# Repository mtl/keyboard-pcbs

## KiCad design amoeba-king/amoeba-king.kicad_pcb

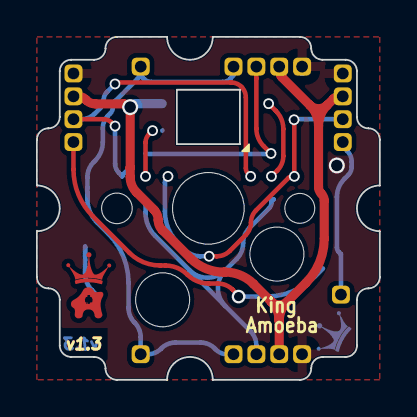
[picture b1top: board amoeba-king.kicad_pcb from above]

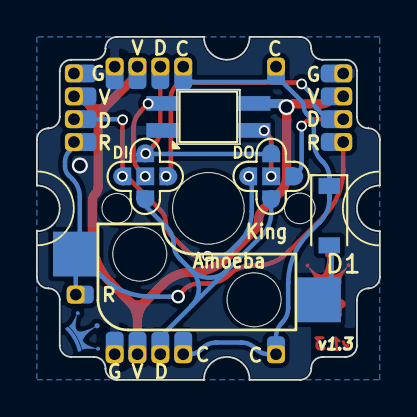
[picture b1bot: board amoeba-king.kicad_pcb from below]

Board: 2 copper layers, 19.0 x 19.1 mm, 15 parts (13 on the bottom side), 10 nets.

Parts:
Amoeba-Logo-Small: G***; amoeba-logo-small
D1: 1N4148W-7-F; D_SOD-123
J1, J4: Conn_01x04_Male; Header_1x04_P1.27mmL
J2, J3: Conn_01x04_Male; Header_1x04_P1.27mm
J5, J6, J7: Conn_01x01_Male; Header_1x01_P1.27mm
JP1, JP2: SolderJumper_5; SolderJumper-5_P1.3mm_Open_RoundedPad1.0x1.5mm
LED1: SK6812MINI_E; LED_SK6812MINI_E_PLCC4_3.2x2.8mm_Shine_Through
Royale: G***; royale
Royale#2: G***; royale
S1: MX1A; Kailh_MX_Socket

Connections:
/C: D1.1 (K), J2.1, J4.1, J5.1, J6.1
/DIN: JP1.2 (C), LED1.4 (DIN)
/GND: J1.4, J2.4, J3.4, J4.4, LED1.3 (VSS)
/R: J1.1, J3.1, J7.1, JP2.2 (C), S1.1
/VDD: J1.3, J2.3, J3.3, J4.3, LED1.1 (VDD)
unnamed: D1.2 (A), S1.2
unnamed: J1.2, JP1.1 (A), JP2.1 (A)
unnamed: J2.2, JP1.5 (E), JP2.5 (E)
unnamed: J3.2, JP1.3 (B), JP2.3 (B)
unnamed: J4.2, JP1.4 (D), JP2.4 (D)

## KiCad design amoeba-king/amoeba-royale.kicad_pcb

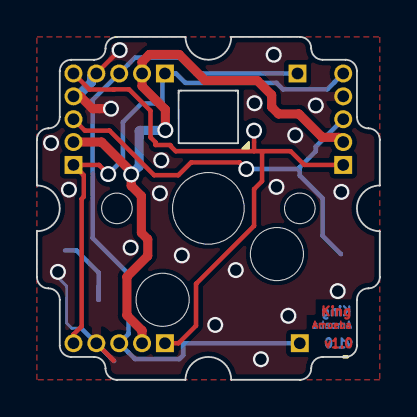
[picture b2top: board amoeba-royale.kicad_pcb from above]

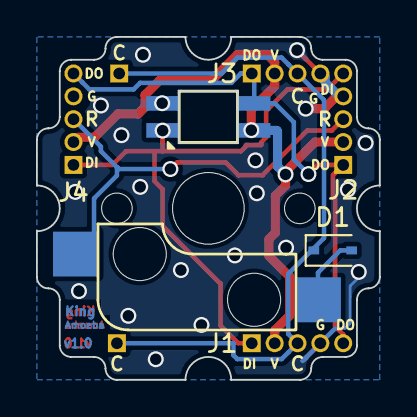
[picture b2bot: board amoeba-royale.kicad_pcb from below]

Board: 2 copper layers, 19.0 x 19.1 mm, 9 parts (9 on the bottom side), 7 nets.

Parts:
D1: 1N4148W-7-F; D_SOD-323
J1, J2, J4: Conn_01x05_Male; Header_1x05_P1.27mm
J3: Conn_01x04_Male; Header_1x04_P1.27mm
J5, J6: Conn_01x01_Male; Header_1x01_P1.27mm
LED1: SK6812MINI_E; LED_SK6812MINI_E_PLCC4_3.2x2.8mm_Shine_Through
S1: MX1A; Kailh_MX_Socket

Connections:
/C: D1.1, J1.3, J3.3, J5.1, J6.1
/DIN: J1.1, J2.5, J4.1, LED1.4
/DOUT: J1.5, J2.1, J3.1, J4.5, LED1.2
/GND: J1.4, J2.4, J3.4, J4.4, LED1.3
/R: J2.3, J4.3, S1.1
/VDD: J1.2, J2.2, J3.2, J4.2, LED1.1
unnamed: D1.2, S1.2

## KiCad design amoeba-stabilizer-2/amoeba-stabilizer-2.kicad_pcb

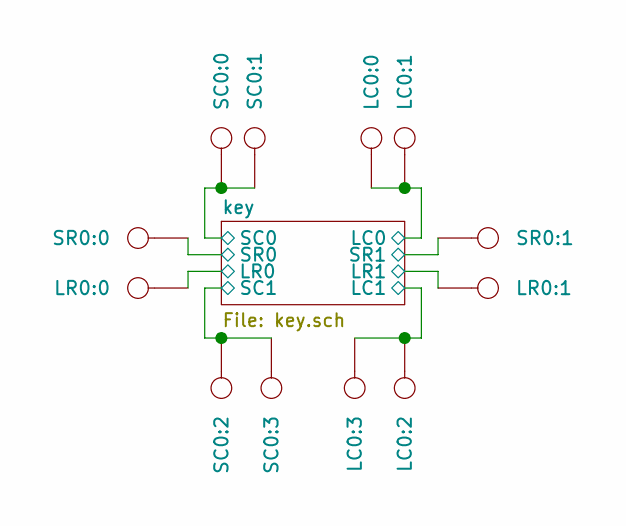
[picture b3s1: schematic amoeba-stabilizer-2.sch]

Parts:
LC0:0, LC0:1, LC0:2, LC0:3: CONN_1
LR0:0, LR0:1: CONN_1
SC0:0, SC0:1, SC0:2, SC0:3: CONN_1
SR0:0, SR0:1: CONN_1

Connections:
/key/LC0: LC0:0.1, LC0:1.1, LC0:2.1, LC0:3.1; also elsewhere on the board
/key/LR0: LR0:0.1, LR0:1.1; also elsewhere on the board
/key/SC0: SC0:0.1, SC0:1.1, SC0:2.1, SC0:3.1; also elsewhere on the board
/key/SR0: SR0:0.1, SR0:1.1; also elsewhere on the board

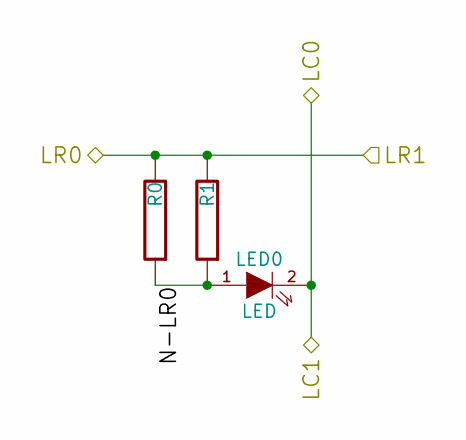
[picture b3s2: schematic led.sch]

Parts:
LED0: LED
R0, R1: RESISTOR

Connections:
/key/LC0: LED0.2 (K); also elsewhere on the board
/key/LR0: R0.2, R1.2; also elsewhere on the board
/key/led/N-LR0: LED0.1 (A), R0.1, R1.1

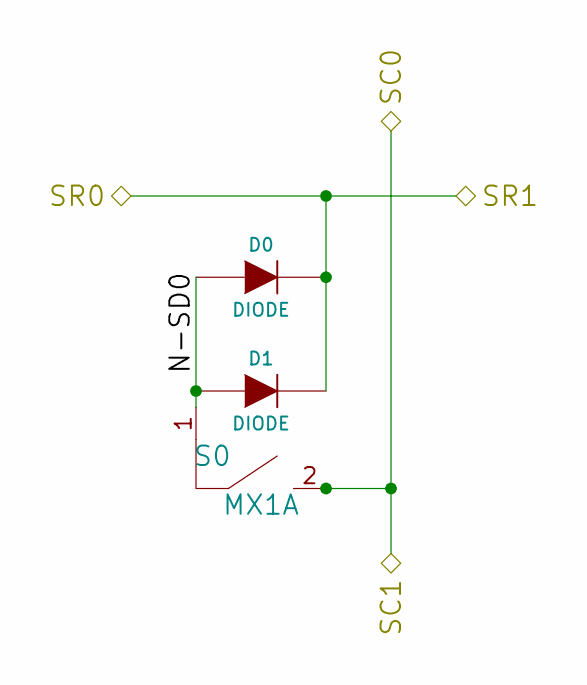
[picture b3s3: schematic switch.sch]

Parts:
D0, D1: DIODE
S0: MX1A

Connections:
/key/SC0: S0.2; also elsewhere on the board
/key/SR0: D0.2 (K), D1.2 (K); also elsewhere on the board
/key/switch/N-SD0: D0.1 (A), D1.1 (A), S0.1

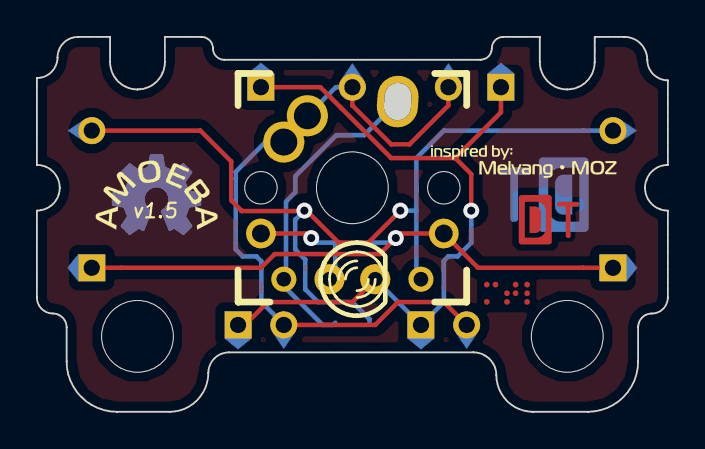
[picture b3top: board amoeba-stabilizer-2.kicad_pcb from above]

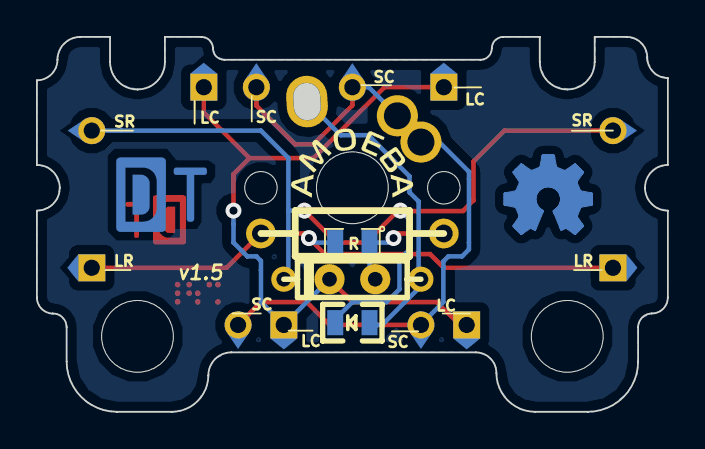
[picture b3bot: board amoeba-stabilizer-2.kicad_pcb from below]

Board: 2 copper layers, 35.1 x 20.8 mm, 38 parts (16 on the bottom side), 6 nets.

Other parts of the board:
amoeba-round: G***; amoeba-round
amoeba-round-rev: G***; amoeba-round-rev
dt-logo-big-rev: G***; dt-logo-big-rev
dt-logo-d: G***; dt-logo-d
dt-logo-t: G***; dt-logo-t
labels-melvang-moz: G***; labels-melvang-moz
mtl-braille: G***; mtl-braille
osh-logo-rev: G***; osh-logo-rev
pad-arrow-round: G***; pad-arrow-round
pad-arrow-round#2, pad-arrow-round#3, pad-arrow-round#4, pad-arrow-round#5, pad-arrow-round#6: G***; pad-arrow-round
pad-arrow-square: G***; pad-arrow-square
pad-arrow-square#2, pad-arrow-square#3, pad-arrow-square#4, pad-arrow-square#5, pad-arrow-square#6: G***; pad-arrow-square

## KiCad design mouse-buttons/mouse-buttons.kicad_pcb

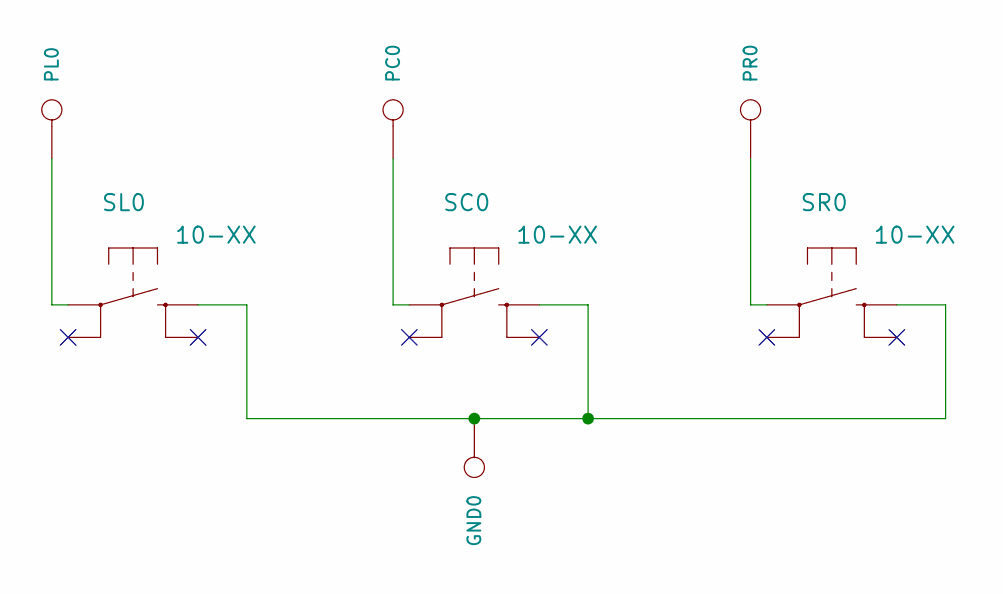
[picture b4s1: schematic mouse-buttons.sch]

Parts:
GND0: CONN_1
PC0: CONN_1
PL0: CONN_1
PR0: CONN_1
SC0: 10-XX; switch-omron-B3F-10XX
SL0: 10-XX; switch-omron-B3F-10XX
SR0: 10-XX; switch-omron-B3F-10XX

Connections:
unnamed: PL0.1, SL0.3
unnamed: PC0.1, SC0.3
unnamed: PR0.1, SR0.3
unnamed: GND0.1, SC0.1 (S), SL0.1 (S), SR0.1 (S)

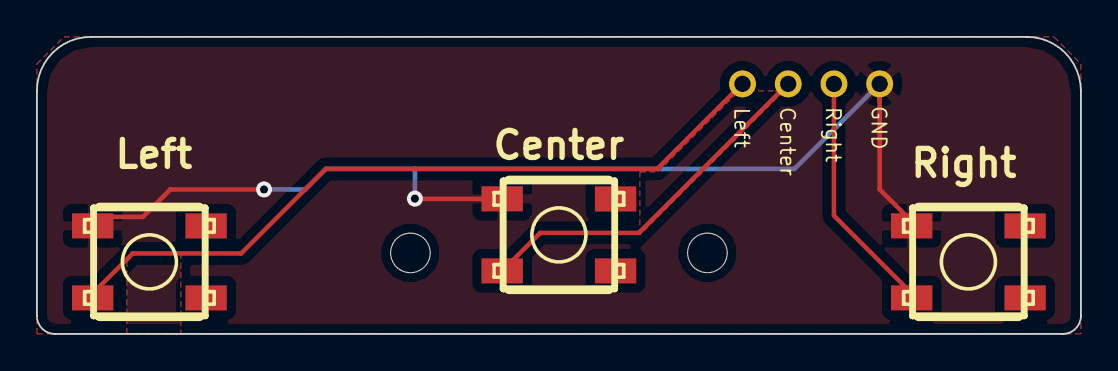
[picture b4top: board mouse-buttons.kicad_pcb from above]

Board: 2 copper layers, 58.0 x 16.5 mm, 7 parts (0 on the bottom side), 4 nets.

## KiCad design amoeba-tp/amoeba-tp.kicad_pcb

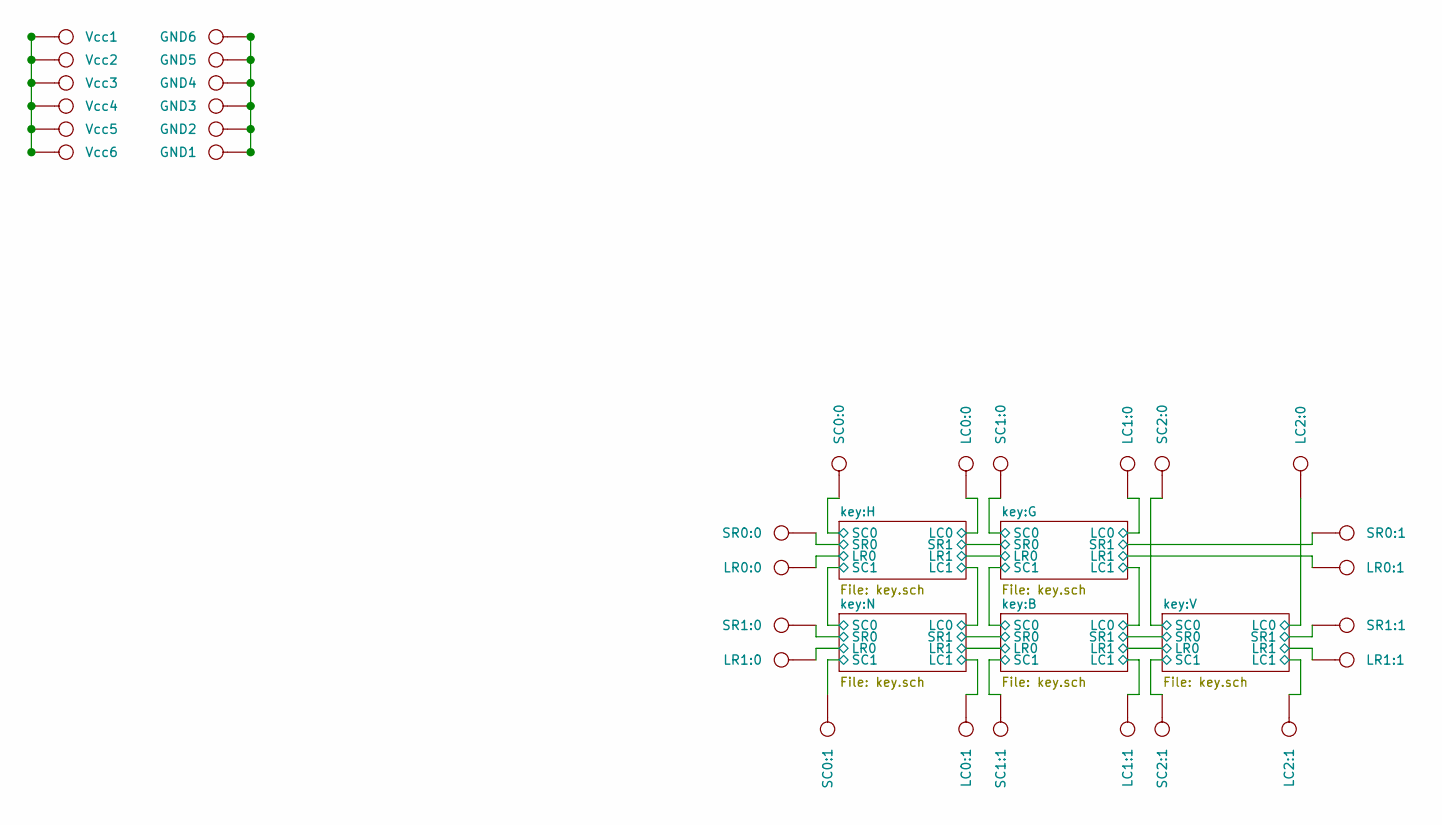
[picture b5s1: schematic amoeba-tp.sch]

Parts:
GND1, GND2, GND3, GND4, GND5, GND6: CONN_1
LC0:0, LC0:1, LC1:0, LC1:1, LC2:0, LC2:1: CONN_1
LR0:0, LR0:1, LR1:0, LR1:1: CONN_1
SC0:0, SC0:1, SC1:0, SC1:1, SC2:0, SC2:1: CONN_1
SR0:0, SR0:1, SR1:0, SR1:1: CONN_1
Vcc1, Vcc2, Vcc3, Vcc4, Vcc5, Vcc6: CONN_1

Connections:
/key:B/LC0: LC1:0.1, LC1:1.1; also elsewhere on the board
/key:B/LR0: LR1:0.1, LR1:1.1; also elsewhere on the board
/key:B/SC0: SC1:0.1, SC1:1.1; also elsewhere on the board
/key:B/SR0: SR1:0.1, SR1:1.1; also elsewhere on the board
/key:G/LR0: LR0:0.1, LR0:1.1; also elsewhere on the board
/key:G/SR0: SR0:0.1, SR0:1.1; also elsewhere on the board
/key:H/LC0: LC0:0.1, LC0:1.1; also elsewhere on the board
/key:H/SC0: SC0:0.1, SC0:1.1; also elsewhere on the board
/key:V/LC0: LC2:0.1, LC2:1.1; also elsewhere on the board
/key:V/SC0: SC2:0.1, SC2:1.1; also elsewhere on the board
unnamed: Vcc1.1, Vcc2.1, Vcc3.1, Vcc4.1, Vcc5.1, Vcc6.1
unnamed: GND1.1, GND2.1, GND3.1, GND4.1, GND5.1, GND6.1

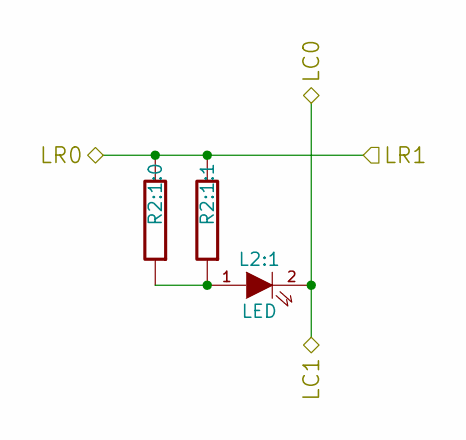
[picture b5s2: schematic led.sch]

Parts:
L0:0: LED
R0:0:0, R0:0:1: RESISTOR

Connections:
/key:G/LR0: R0:0:0.2, R0:0:1.2; also elsewhere on the board
/key:H/LC0: L0:0.2 (K); also elsewhere on the board
unnamed: L0:0.1 (A), R0:0:0.1, R0:0:1.1

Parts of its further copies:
L0:1, L1:0, L1:1, L2:1: LED
R0:1:0, R0:1:1, R1:0:0, R1:0:1, R1:1:0, R1:1:1, R2:1:0, R2:1:1: RESISTOR

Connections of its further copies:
/key:B/LC0: L1:0.2 (K), L1:1.2 (K); also elsewhere on the board
/key:B/LR0: R0:1:0.2, R0:1:1.2, R1:1:0.2, R1:1:1.2, R2:1:0.2, R2:1:1.2; also elsewhere on the board
/key:G/LR0: R1:0:0.2, R1:0:1.2; also elsewhere on the board
/key:H/LC0: L0:1.2 (K); also elsewhere on the board
/key:V/LC0: L2:1.2 (K); also elsewhere on the board
unnamed: L1:0.1 (A), R1:0:0.1, R1:0:1.1
unnamed: L0:1.1 (A), R0:1:0.1, R0:1:1.1
unnamed: L1:1.1 (A), R1:1:0.1, R1:1:1.1
unnamed: L2:1.1 (A), R2:1:0.1, R2:1:1.1

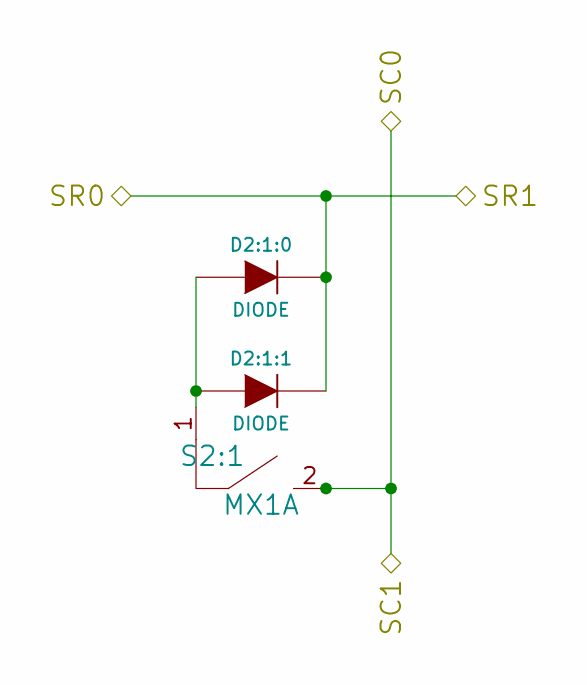
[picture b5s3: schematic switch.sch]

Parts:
D0:0:0, D0:0:1: DIODE
S0:0: MX1A

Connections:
/key:G/SR0: D0:0:0.2 (K), D0:0:1.2 (K); also elsewhere on the board
/key:H/SC0: S0:0.2; also elsewhere on the board
unnamed: D0:0:0.1 (A), D0:0:1.1 (A), S0:0.1

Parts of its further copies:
D0:1:0, D0:1:1, D1:0:0, D1:0:1, D1:1:0, D1:1:1, D2:1:0, D2:1:1: DIODE
S0:1, S1:0, S1:1, S2:1: MX1A

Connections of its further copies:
/key:B/SC0: S1:0.2, S1:1.2; also elsewhere on the board
/key:B/SR0: D0:1:0.2 (K), D0:1:1.2 (K), D1:1:0.2 (K), D1:1:1.2 (K), D2:1:0.2 (K), D2:1:1.2 (K); also elsewhere on the board
/key:G/SR0: D1:0:0.2 (K), D1:0:1.2 (K); also elsewhere on the board
/key:H/SC0: S0:1.2; also elsewhere on the board
/key:V/SC0: S2:1.2; also elsewhere on the board
unnamed: D1:0:0.1 (A), D1:0:1.1 (A), S1:0.1
unnamed: D0:1:0.1 (A), D0:1:1.1 (A), S0:1.1
unnamed: D1:1:0.1 (A), D1:1:1.1 (A), S1:1.1
unnamed: D2:1:0.1 (A), D2:1:1.1 (A), S2:1.1

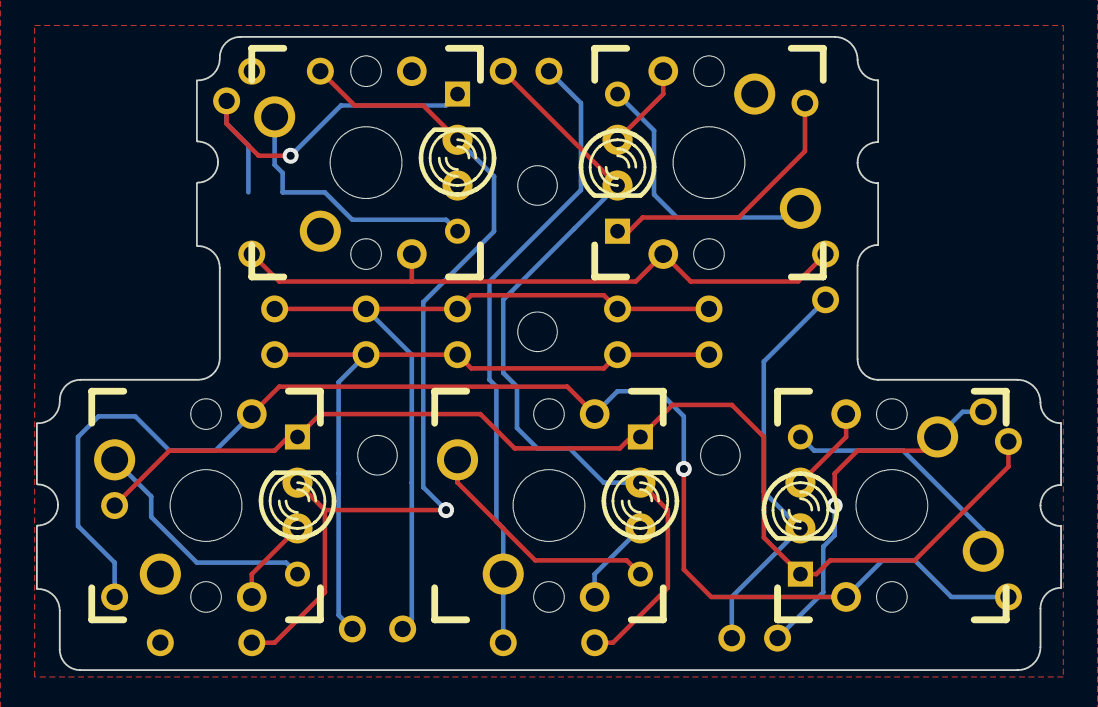
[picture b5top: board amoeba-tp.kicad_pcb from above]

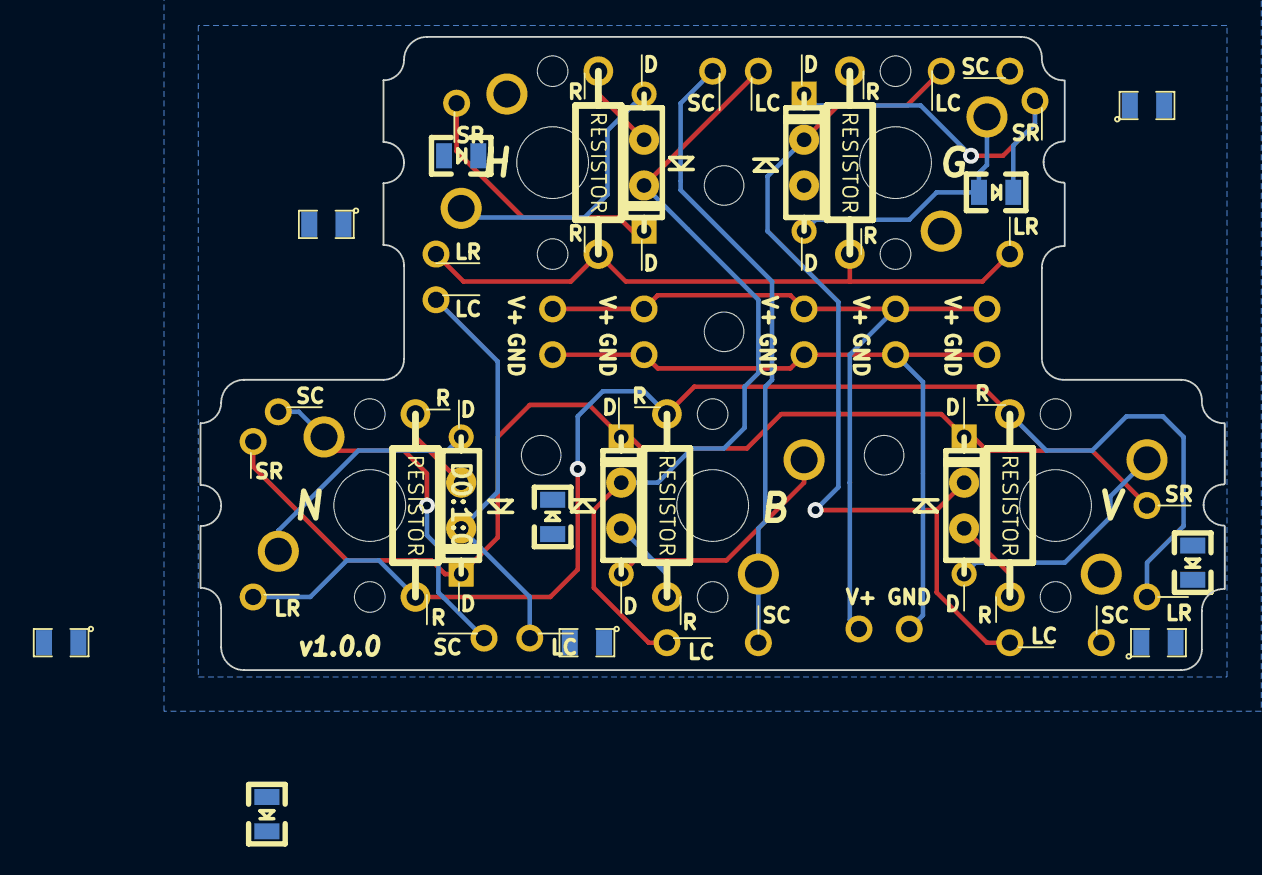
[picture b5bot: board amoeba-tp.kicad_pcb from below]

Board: 2 copper layers, 56.9 x 35.2 mm, 62 parts (20 on the bottom side), 22 nets.

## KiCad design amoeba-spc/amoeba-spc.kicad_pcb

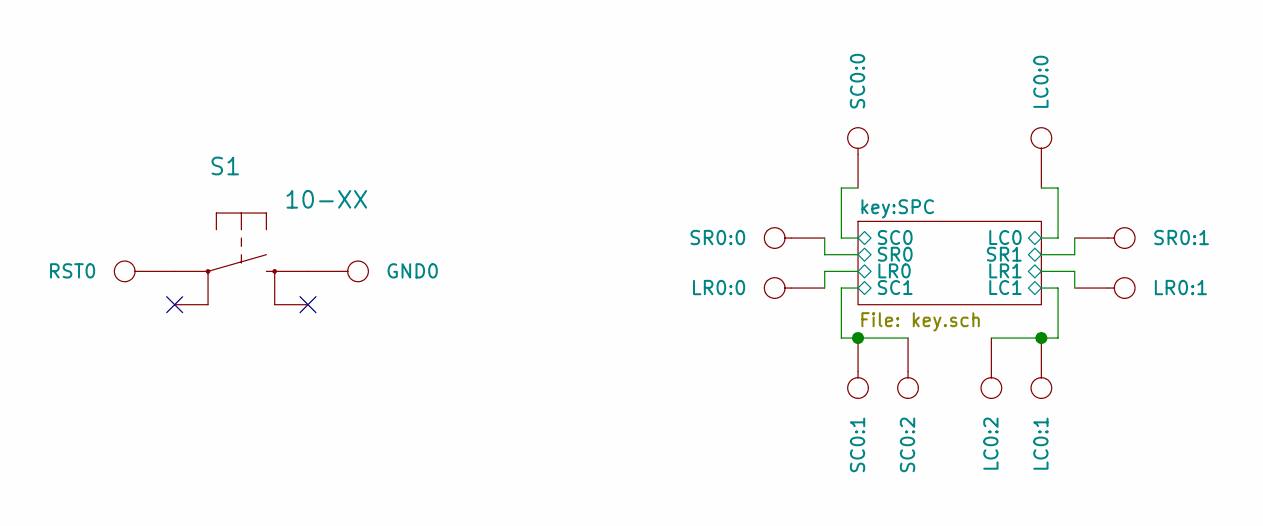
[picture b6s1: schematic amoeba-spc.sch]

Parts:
GND0: CONN_1
LC0:0, LC0:1, LC0:2: CONN_1
LR0:0, LR0:1: CONN_1
RST0: CONN_1
S1: 10-XX; switch-omron-B3F-10XX
SC0:0, SC0:1, SC0:2: CONN_1
SR0:0, SR0:1: CONN_1

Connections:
/key:SPC/LC0: LC0:0.1, LC0:1.1, LC0:2.1; also elsewhere on the board
/key:SPC/LR0: LR0:0.1, LR0:1.1; also elsewhere on the board
/key:SPC/SC0: SC0:0.1, SC0:1.1, SC0:2.1; also elsewhere on the board
/key:SPC/SR0: SR0:0.1, SR0:1.1; also elsewhere on the board
unnamed: GND0.1, S1.1 (S)
unnamed: RST0.1, S1.3

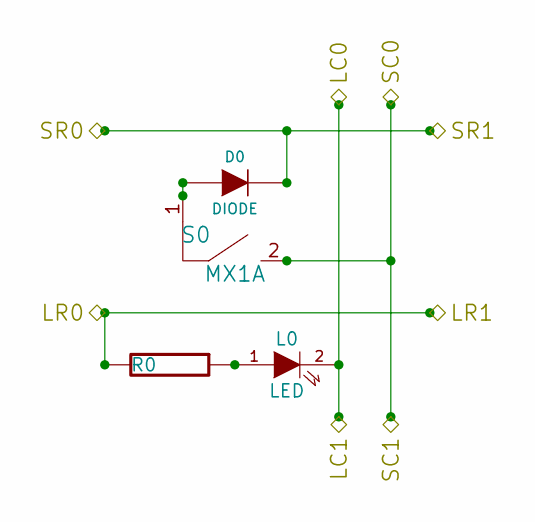
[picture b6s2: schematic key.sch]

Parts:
D0: DIODE
L0: LED
R0: RESISTOR
S0: MX1A

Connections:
/key:SPC/LC0: L0.2 (K); also elsewhere on the board
/key:SPC/LR0: R0.2; also elsewhere on the board
/key:SPC/SC0: S0.2; also elsewhere on the board
/key:SPC/SR0: D0.2 (K); also elsewhere on the board
unnamed: D0.1 (A), S0.1
unnamed: L0.1 (A), R0.1

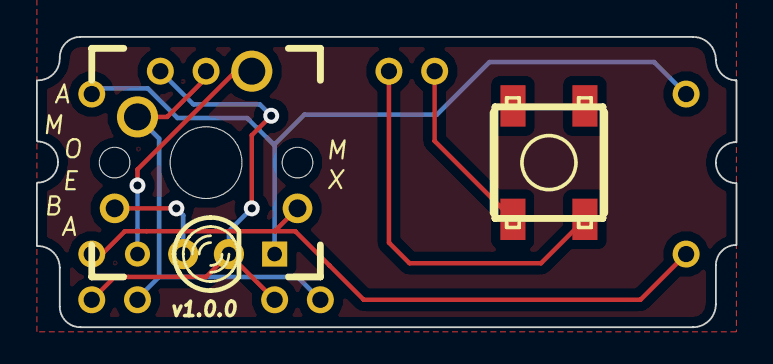
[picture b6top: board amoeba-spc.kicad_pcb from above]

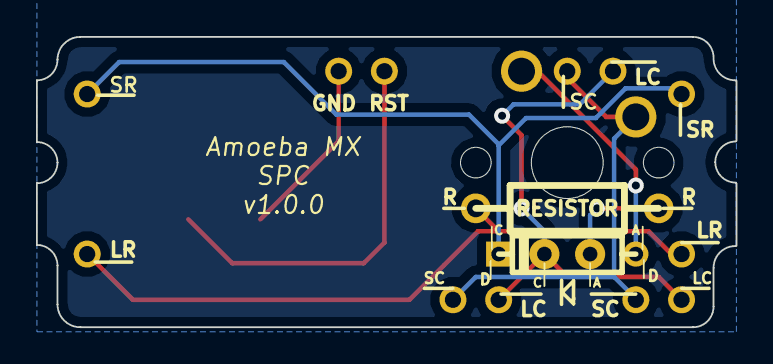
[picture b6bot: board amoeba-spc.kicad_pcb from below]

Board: 2 copper layers, 38.9 x 16.1 mm, 17 parts (2 on the bottom side), 8 nets.

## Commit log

2015-08-20 Initial commit. Amoeba v1.0.0 PCB.
2015-08-21 Labeling improvements to amoeba.
2015-08-22 Adding Amoeba-TP PCB.
2015-08-22 Added fill zones.
2015-08-22 Add labels to PCB and remove Amoeba footprints.
2015-08-23 Cleaned up Amoeba TP design.
2015-08-23 Cleaned up Amoeba PCB.
2015-08-23 Shared libraries and modules directories.
2015-08-23 Adding Makefiles.
2015-08-23 Adding Amoeba-spc PCB
2015-08-24 Makefile improvements.
2015-08-24 Fixes for Oshpark submission and minor labeling adjustments.
2015-08-24 Removed excess junctions.
2015-08-24 Moved licence file(s) into proper places.
2015-08-24 Added surface mount pads to Amoeba and bumped version number to 1.1.0.
2015-08-24 Updating labels and SMD diode module.
2015-08-24 Fixed edge cut connectivity in Amoeba MX.
2015-08-25 Fix broken kicad from Mac edit.
2015-08-25 Split key schematic into multiple sheets.
2015-08-25 Schematic clean-up.
2015-08-25 Adding SMD options to TP module.
2015-08-26 Adding mouse buttons PCB.
2015-08-26 .gitignore update.
2015-08-27 Revised mouse buttons PCB and added precise measurements for mouse buttons and TrackPoint holes.
2015-08-28 Added Alps support to Amoeba. Upped version # to v.1.2.0
2015-08-28 Minor edits to amoeba.
2015-08-28 Improved placement of SMD diode and resistor on amoeba.
2015-08-28 Silkscreen edits.
2015-08-28 Renaming module to avoid name collision on case-insensitive file systems.
2015-09-15 More changes for amoeba 1.2.1.
2015-09-15 Adding net names to amoeba.
2015-09-15 Minor clean-up.
2015-09-15 Added DT logo to amoeba.
2015-09-17 Adding amoeba stabilizer 2u pcb.
2015-09-17 Widened 2u pcb.
2015-09-20 Improved DT logos on amoeba.
2015-09-20 Improvements to DT logo module.
2015-09-20 Added names to silkscreen and copper layers.
2015-09-21 Adding svg2mod script.
2015-09-21 Added command line argument parsing to svg2mod.
2015-09-22 svg2mod using svg library
2015-09-22 Adding test SVG.
2015-09-22 Improvements to svg2mod
2015-09-23 Added support for pretty format (not tested).
2015-09-23 Added support for mm units in legacy format, and other improvements.
2015-09-23 Added support for outline stroke width.
2015-10-06 Update amoeba 1u to v1.3. Remove svg2mod (now kept in a separate repository.
2015-10-10 Adding SVG files and associated Makefile.
2015-10-12 Updated amoeba PCB with svg modules.
2015-10-31 Updates to amoeba 1u and 2u.
2015-11-01 Added copper fill keepout zone around OSH logo.
2015-11-21 Added pad arrows.
2015-11-21 Fix oversized mask on pad arrows.
2015-11-23 Tighten solder masks, add pad arrows to amoeba-stabilizer-2, convert amoeba on 2u to copper.
2015-11-23 Replaced OSH logo.
2015-11-23 Centered amoeba text.
2015-11-23 Slight improvement to keepout zone.
2016-01-05 Update to version 1.5.
2020-04-11 Adding Amoeba v2.0 gerbers.
2020-04-11 Adding Amoeba v2.0 sources.
2020-05-18 First implementation of amoeba-king single
    HotSwap
    Bus based connections for Diode+R/C
    SMD LED
    SMD Diode
2020-05-18 Getting closer
    3d View still has pins :(
2020-05-18 Getting ready for final review, before sending for production
2020-05-19 Initial Order
2020-05-19 Ignore ZIP files
2020-05-19 Added initial BOM
2020-05-19 Final order
2020-05-27 Fixed inverted SMD LED Layout
2020-05-27 Various Layout Improvements
2020-05-27 Getting pretty close to v1.1 improved Pads
2020-05-28 Getting closer to production of 1.1
    bigger pads, smaller jumpers
2020-05-28 Offset the mounting holes to make more space for cabling
2020-06-01 Added initial OpenSCAD 3D model of key slot
2020-06-02 Adding more functions for SCAD model
2020-06-02 Added files sent for v1.1 production
2020-06-03 Getting closer to ergoodx scad
2020-06-03 Added 2U support
2020-06-03 More tweaks to 2U key
2020-06-04 More design revisions
2020-06-08 Getting closer
2020-06-09 Mork work on viable numpad
2020-07-31 Minor tweaks
2020-07-31 Default to Ergo Dactyl
2022-07-30 Version 1.2 of the king amoeba.
2022-07-30 Redone zones.
2022-07-30 Moved via to the center of the pad.
2022-07-30 Cleanup tracks.
2022-07-31 Checkpoint commit.
2022-09-23 Rounded tracks, and gerber file.
2022-09-25 Moved some graphics for better legibility.
2022-10-02 Added row via to be used as an anchor point for cabling.
